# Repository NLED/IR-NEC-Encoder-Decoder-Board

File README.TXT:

THERE IS NO WARRANTY FOR THE PROGRAM, TO THE EXTENT PERMITTED BY APPLICABLE LAW. 
EXCEPT WHEN OTHERWISE STATED IN WRITING THE COPYRIGHT HOLDERS AND/OR OTHER PARTIES 
PROVIDE THE PROGRAM “AS IS” WITHOUT WARRANTY OF ANY KIND, EITHER EXPRESSED OR IMPLIED,
INCLUDING, BUT NOT LIMITED TO, THE IMPLIED WARRANTIES OF MERCHANTABILITY AND FITNESS 
FOR A PARTICULAR PURPOSE. THE ENTIRE RISK AS TO THE QUALITY AND PERFORMANCE OF THE 
PROGRAM IS WITH YOU. SHOULD THE PROGRAM PROVE DEFECTIVE, YOU ASSUME THE COST OF ALL 
NECESSARY SERVICING, REPAIR OR CORRECTION.

 Original Author: Jeffrey Nygaard
 Company: Northern Lights Electronic Design, LLC
 Date: May 5, 2018
 Contact: JNygaard@NLEDshop.com
 Copyright© 2018 by Northern Lights Electronic Design, LLC. All Rights Reserved
 
;=============          www.NLEDShop.com/addoncards           ============
;=============     www.NorthernLightsElectronicDesign.com       ============

This work is licensed under a Attribution-NonCommercial 4.0 International (CC BY-NC 4.0)
https://creativecommons.org/licenses/by-nc/4.0/legalcode

Free to use for personal use, but please attribute the original author.

Commercial licenses versions are available for a donation of any amount. Contact JNygaard@NLEDshop.com for details.

================================================================================================================

Ready-made devices are available for purchase, and large batch manufacturing of any device can be requested.
Please see the webpage www.NLEDShop.com/addoncards

NLED is available for custom design and manufacturing, please contact via phone or email to discuss your project.

================================================================================================================

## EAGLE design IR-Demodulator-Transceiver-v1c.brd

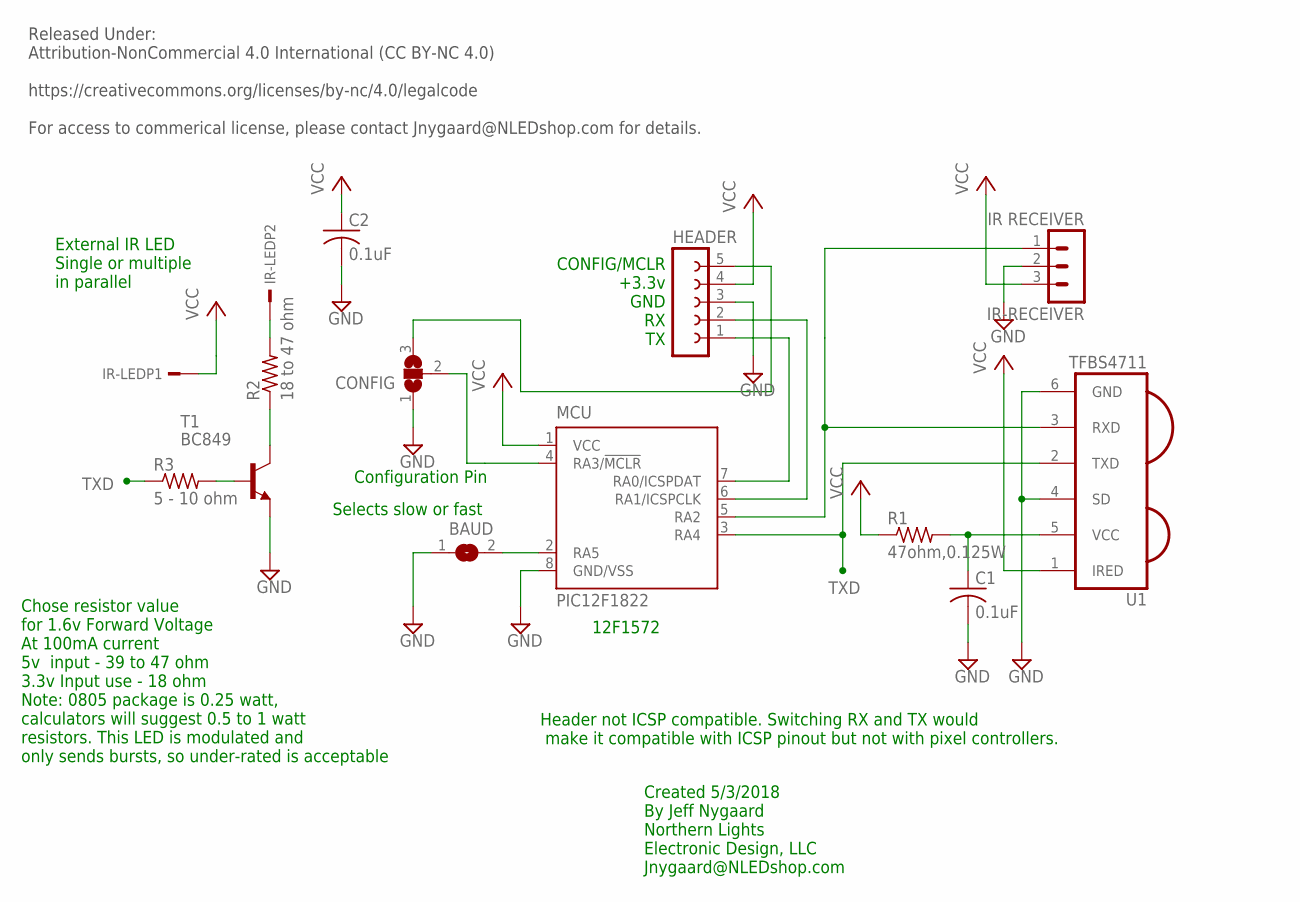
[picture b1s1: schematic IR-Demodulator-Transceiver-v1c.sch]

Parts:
BAUD: SJ
C1, C2: 0.1uF; C0805
CONFIG: SJ2W; SJ_2
HEADER: FE05-1
IR-LED: HEADER-2X1
IR-RECEIVER: IR RECEIVER; MA03-1
MCU: PIC12F1822; SOIC-8
R1: 47ohm,0.125W; R0805
R2: 18 to 47 ohm; R0805
R3: 5 - 10 ohm; R0603
T1: BC849; SOT23
U1: TFBS4711

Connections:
GND: BAUD.1, C1.2, C2.2, CONFIG.1, HEADER.3, IR-RECEIVER.2, MCU.8 (GND/VSS), T1.2 (E), U1.4 (SD), U1.6 (GND)
IRRX: IR-RECEIVER.1, MCU.5 (RA2), U1.3 (RXD)
unnamed: R3.2, T1.1 (B)
unnamed: BAUD.2, MCU.2 (RA5)
unnamed: C1.1, R1.2, U1.5 (VCC)
unnamed: CONFIG.3, HEADER.5
unnamed: HEADER.1, MCU.7 (RA0/ICSPDAT)
unnamed: HEADER.2, MCU.6 (RA1/ICSPCLK)
unnamed: CONFIG.2, MCU.4 (RA3/!MCLR)
unnamed: IR-LED.2, R2.2
unnamed: R2.1, T1.3 (C)
TXD: MCU.3 (RA4), R3.1, U1.2 (TXD)
VCC: C2.1, HEADER.4, IR-LED.1, IR-RECEIVER.3, MCU.1 (VCC), R1.1, U1.1 (IRED)

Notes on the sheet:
CONFIG/MCLR +3.3v GND RX TX
Selects slow or fast
Configuration Pin
Header not ICSP compatible. Switching RX and TX would make it compatible with ICSP pinout but not with pixel controllers.
External IR LED Single or multiple in parallel
Chose resistor value for 1.6v Forward Voltage At 100mA current 5v input - 39 to 47 ohm 3.3v Input use - 18 ohm Note: 0805 package is 0.25 watt, calculators will suggest 0.5 to 1 watt resistors. This LED is modulated and only sends bursts, so under-rated is acceptable
12F1572
Released Under: Attribution-NonCommercial 4.0 International (CC BY-NC 4.0) https://creativecommons.org/licenses/by-nc/4.0/legalcode For access to commerical license, please contact Jnygaard@NLEDshop.com for details.
Created 5/3/2018 By Jeff Nygaard Northern Lights Electronic Design, LLC Jnygaard@NLEDshop.com

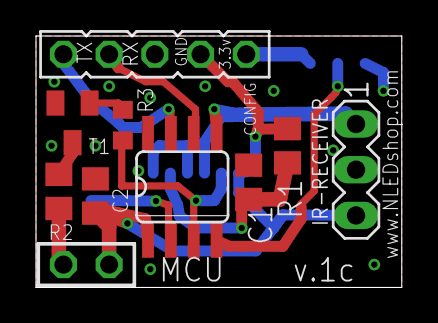
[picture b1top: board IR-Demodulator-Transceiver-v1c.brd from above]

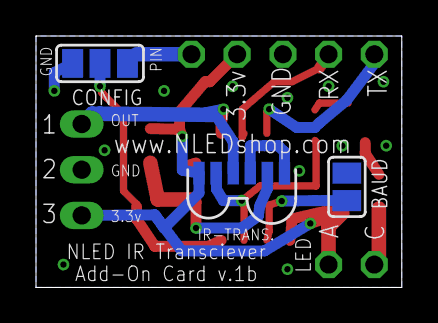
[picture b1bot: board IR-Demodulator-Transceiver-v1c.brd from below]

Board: 2 copper layers, 20.3 x 14.0 mm, 13 parts (3 on the bottom side), 13 nets.

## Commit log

2018-05-03 Initial
2018-05-03 Other Files

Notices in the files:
parts and their libraries:
vishay: Copyright (C) 2014, Bob Starr
